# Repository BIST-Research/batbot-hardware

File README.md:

# batbot-hardware
schematics and pcbs for the batbot

## batbot-6.5 wiring diagram

## Adafruit itsybitsy M4 pinout

## Grandcentral M4 pinout

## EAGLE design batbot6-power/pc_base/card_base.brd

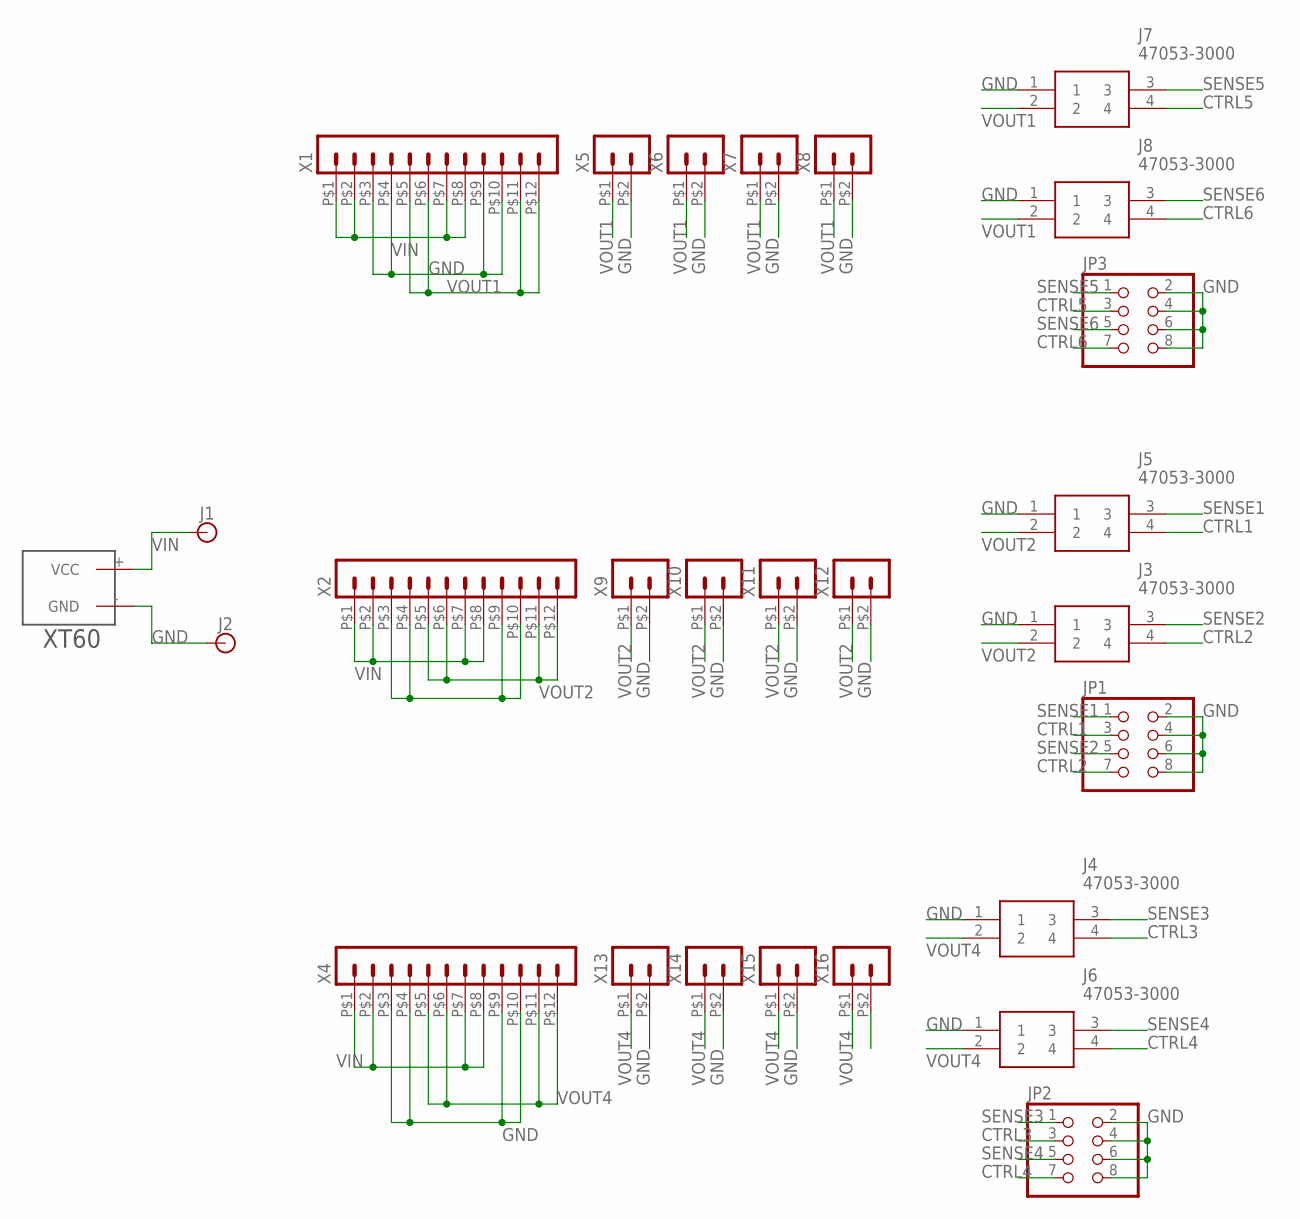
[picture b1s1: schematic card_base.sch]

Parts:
J1, J2: BANANA_CONN
J3, J4, J5, J6, J7, J8: 47053-3000; 470533000
JP1, JP2, JP3: PINHD-2X4; 2X04
U$1: XT60
X1, X2, X4: HEADER_POS12_44432-1201; 44432-1201
X5, X6, X7, X8, X9, X10, X11, X12, X13, X14, X15, X16: HEADER_POS2_44914-0201; 44914-0201

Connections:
CTRL1: J5.4, JP1.3
CTRL2: J3.4, JP1.7
CTRL3: J4.4, JP2.3
CTRL4: J6.4, JP2.7
CTRL5: J7.4, JP3.3
CTRL6: J8.4, JP3.7
GND: J2.P$1, J3.1, J4.1, J5.1, J6.1, J7.1, J8.1, JP1.2, JP1.4, JP1.6, JP1.8, JP2.2, JP2.4, JP2.6, JP2.8, JP3.2, JP3.4, JP3.6, JP3.8, U$1.- (GND), X1.P$3 (3), X1.P$4 (4), X1.P$9 (9), X1.P$10 (10), X2.P$3 (3), X2.P$4 (4), X2.P$9 (9), X2.P$10 (10), X4.P$3 (3), X4.P$4 (4), X4.P$9 (9), X4.P$10 (10), X5.P$2 (2), X6.P$2 (2), X7.P$2 (2), X8.P$2 (2), X9.P$2 (2), X10.P$2 (2), X11.P$2 (2), X12.P$2 (2), X13.P$2 (2), X14.P$2 (2), X15.P$2 (2), X16.P$2 (2)
SENSE1: J5.3, JP1.1
SENSE2: J3.3, JP1.5
SENSE3: J4.3, JP2.1
SENSE4: J6.3, JP2.5
SENSE5: J7.3, JP3.1
SENSE6: J8.3, JP3.5
VIN: J1.P$1, U$1.+ (VCC), X1.P$1 (1), X1.P$2 (2), X1.P$7 (7), X1.P$8 (8), X2.P$1 (1), X2.P$2 (2), X2.P$7 (7), X2.P$8 (8), X4.P$1 (1), X4.P$2 (2), X4.P$7 (7), X4.P$8 (8)
VOUT1: J7.2, J8.2, X1.P$5 (5), X1.P$6 (6), X1.P$11 (11), X1.P$12 (12), X5.P$1 (1), X6.P$1 (1), X7.P$1 (1), X8.P$1 (1)
VOUT2: J3.2, J5.2, X2.P$5 (5), X2.P$6 (6), X2.P$11 (11), X2.P$12 (12), X9.P$1 (1), X10.P$1 (1), X11.P$1 (1), X12.P$1 (1)
VOUT4: J4.2, J6.2, X4.P$5 (5), X4.P$6 (6), X4.P$11 (11), X4.P$12 (12), X13.P$1 (1), X14.P$1 (1), X15.P$1 (1), X16.P$1 (1)

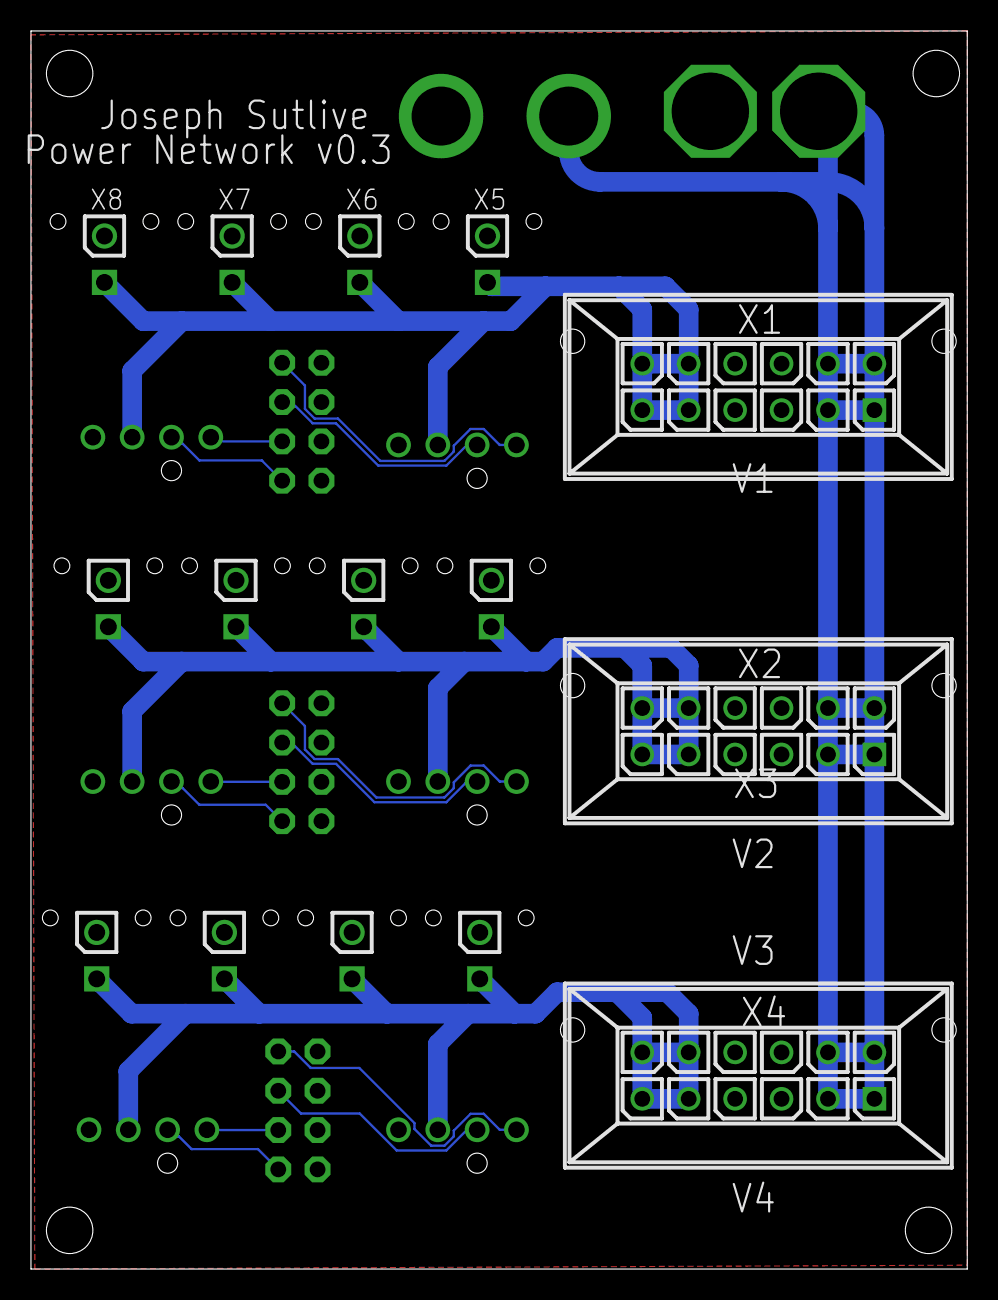
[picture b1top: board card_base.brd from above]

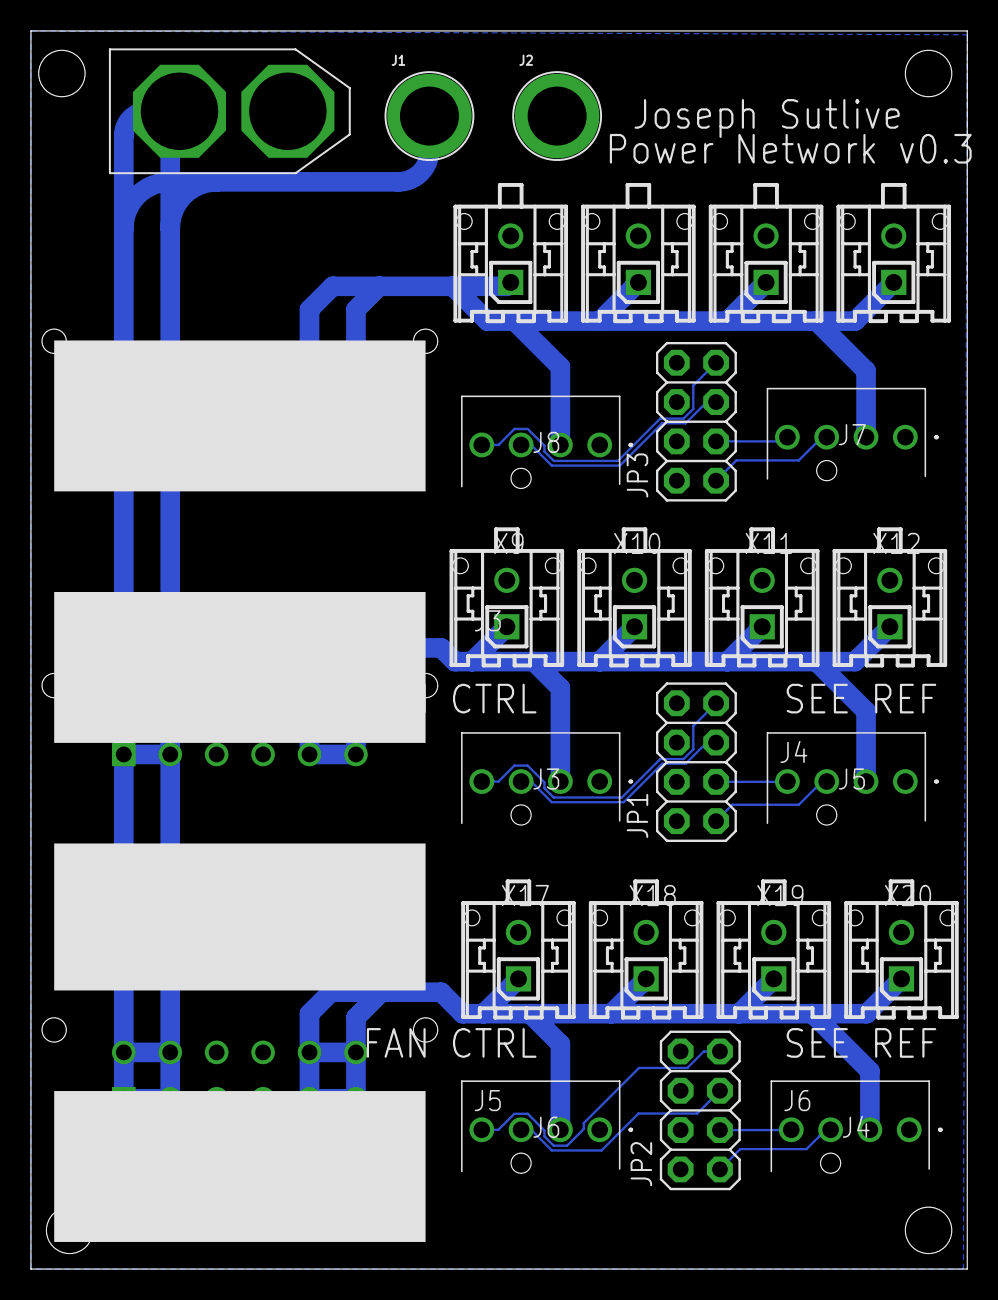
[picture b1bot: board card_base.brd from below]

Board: 2 copper layers, 60.5 x 80.0 mm, 27 parts (24 on the bottom side), 17 nets.

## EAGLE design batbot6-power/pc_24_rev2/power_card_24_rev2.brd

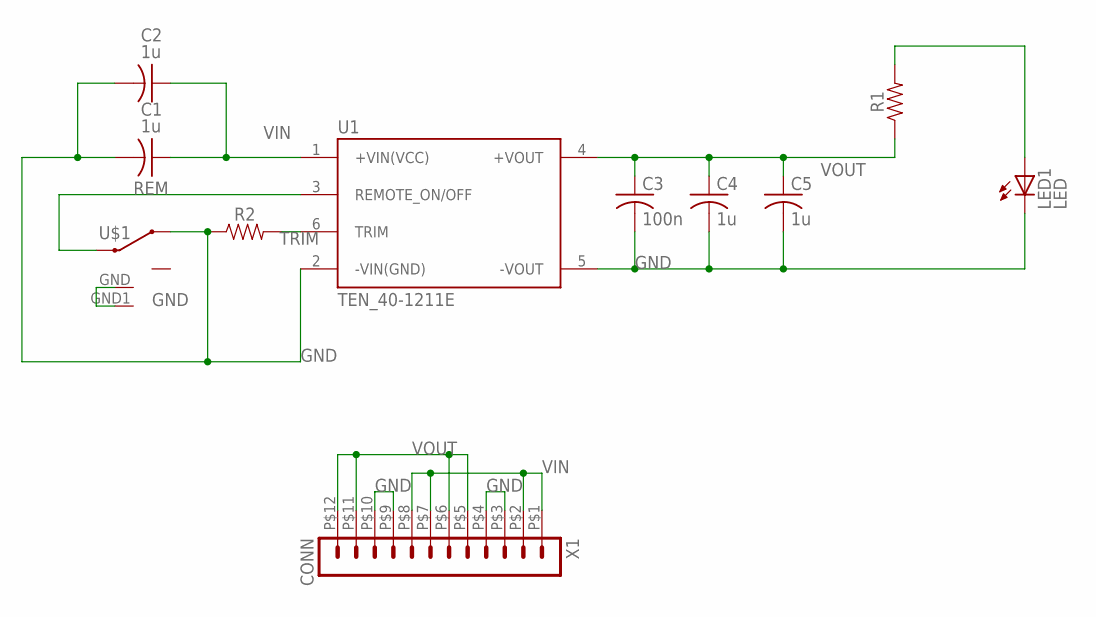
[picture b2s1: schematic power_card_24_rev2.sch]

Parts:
C1, C2, C4, C5: 1u; C1206
C3: 100n; C1206
LED1: LED; LED5MM
R1, R2: 1206
U1: TEN_40-1211E; CONV_TEN_40-1211E
U$1: 1825232-1
X1: CONN; 44764-1201

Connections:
GND: C1.2, C2.2, C3.2, C4.2, C5.2, LED1.K (C), R2.1, U1.2 (-VIN(GND)), U1.5 (-VOUT), U$1.3, U$1.GND, U$1.GND1, X1.P$3 (3), X1.P$4 (4), X1.P$9 (9), X1.P$10 (10)
unnamed: LED1.A, R1.2
REM: U1.3 (REMOTE_ON/OFF), U$1.2
TRIM: R2.2, U1.6 (TRIM)
VIN: C1.1, C2.1, U1.1 (+VIN(VCC)), X1.P$1 (1), X1.P$2 (2), X1.P$7 (7), X1.P$8 (8)
VOUT: C3.1, C4.1, C5.1, R1.1, U1.4 (+VOUT), X1.P$5 (5), X1.P$6 (6), X1.P$11 (11), X1.P$12 (12)

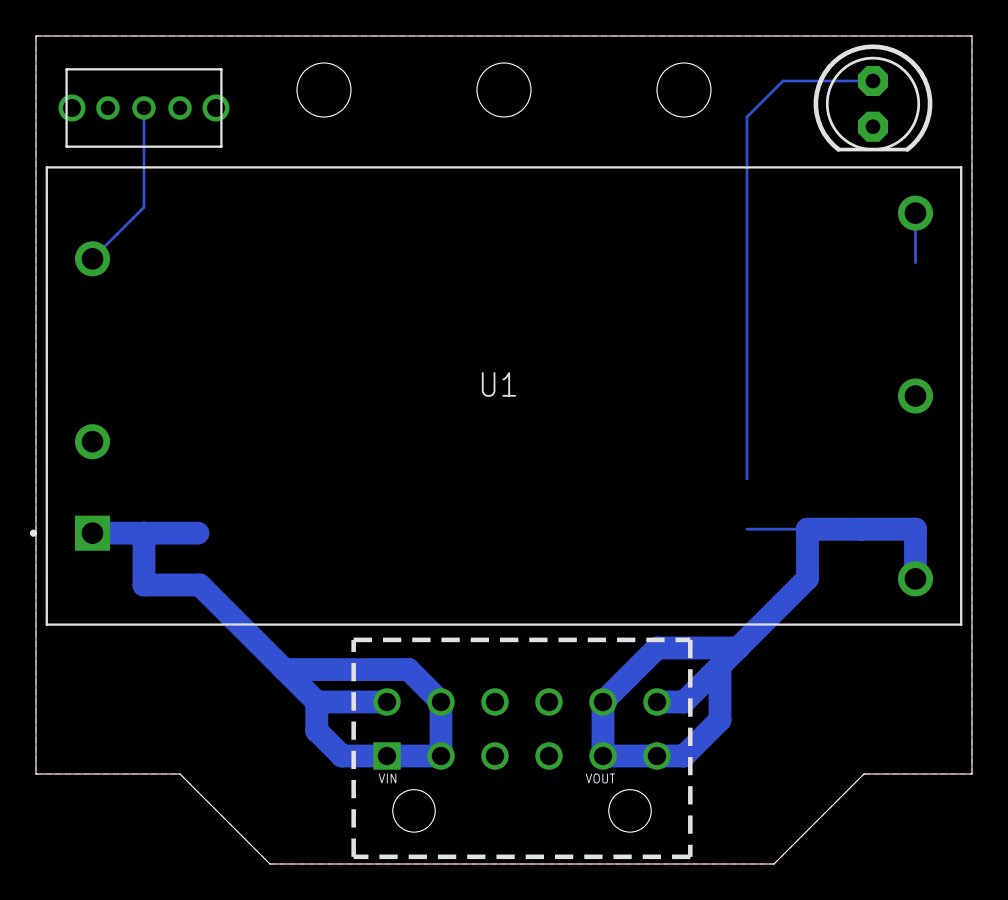
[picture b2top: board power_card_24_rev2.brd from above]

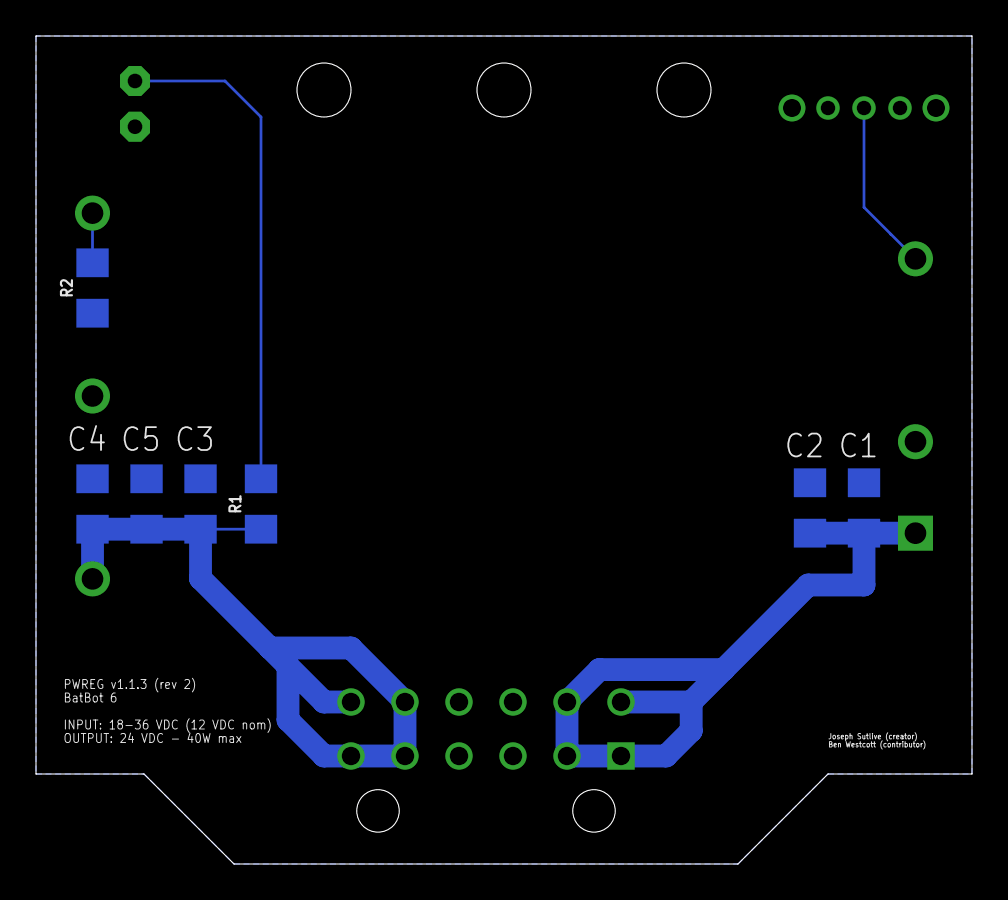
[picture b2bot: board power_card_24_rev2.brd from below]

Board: 2 copper layers, 52.0 x 46.0 mm, 11 parts (7 on the bottom side), 6 nets.

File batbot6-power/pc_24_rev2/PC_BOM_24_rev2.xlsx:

Desc | Value | Designator | Footprint | part # | type
Cap 50V cer 10% | 1u | C1,C2,C4,C5 | 1206 | C1848 | basic
Cap 50V cer 10% | 0u1 | C3 | 1206 | C24497 | basic
Res 250mW 1% | 2k | R1 | 1206 | C17936 | basic
Res 250mW 1% | 470k | R2 | 1206 | C2692714 | extended

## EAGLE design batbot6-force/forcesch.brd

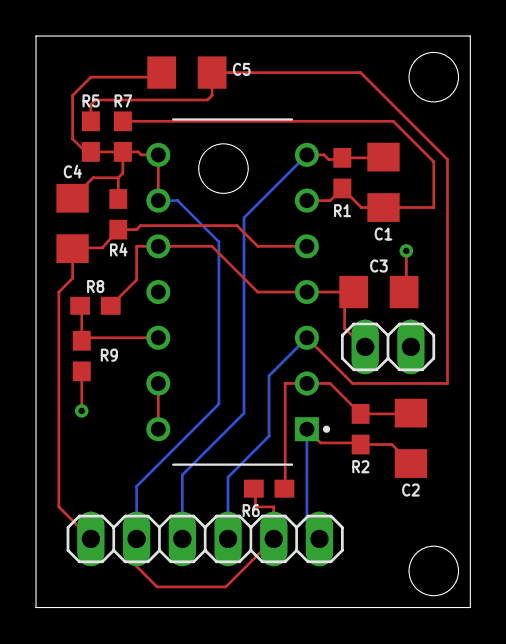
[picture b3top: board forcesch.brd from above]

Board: 2 copper layers, 24.1 x 31.8 mm, 16 parts (0 on the bottom side), 11 nets.

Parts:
C1, C2: 10n; 1206
C3: 0u1; 1206
C4, C5: 100n; 1206
JP1: 1X02
JP4: 1X06
R1, R2: 22k; 0603
R4, R5, R8, R9: 1Meg; 0603
R6, R7: 2k7; 0603
U$1: LM324N/NOPB; DIP825W47P254L1917H533Q14

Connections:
GND: C3.2, JP1.2, R9.1, U$1.11
L-: C2.1, R2.2, R6.2, U$1.2
LIN+: C5.2, JP4.4, R5.1, U$1.3
LOUT: C2.2, JP4.6, R2.1, U$1.1
unnamed: U$1.13, U$1.14
unnamed: R8.1, R9.2, U$1.12
R-: C1.2, R1.1, R7.2, U$1.6
RIN+: C4.1, JP4.1, R4.2, U$1.5
RLIN-: C4.2, C5.1, JP4.2, JP4.5, R4.1, R5.2, R6.1, R7.1, U$1.8, U$1.9
ROUT: C1.1, JP4.3, R1.2, U$1.7
VCC: C3.1, JP1.1, R8.2, U$1.4, U$1.10

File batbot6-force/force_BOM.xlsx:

Desc | Value | Designator | Footprint | part # | type
Cap 50V cer 10% | 10n | C1,C2 | 1206 | C1846 | basic
Cap 50V cer 10% | 100n | C3,C4,C5 | 1206 | C1946 | basic
Res 100mW 1% | 22k | R1,R2 | 0603 | C31850 | basic
Res 100mW 1% | 2k7 | R6,R7 | 0603 | C13167 | basic
Res 100mW 1% | 1Meg | R4,R5,R8,R9 | 0603 | C22935 | basic

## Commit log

2023-09-06 pushing docs/shems/pcbs
2023-09-06 update wd to jpg

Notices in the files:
parts and their libraries:
SparkFun-Capacitors: Licensing: Creative Commons ShareAlike 4.0 International - https://creativecommons.org/licenses/by-sa/4.0
